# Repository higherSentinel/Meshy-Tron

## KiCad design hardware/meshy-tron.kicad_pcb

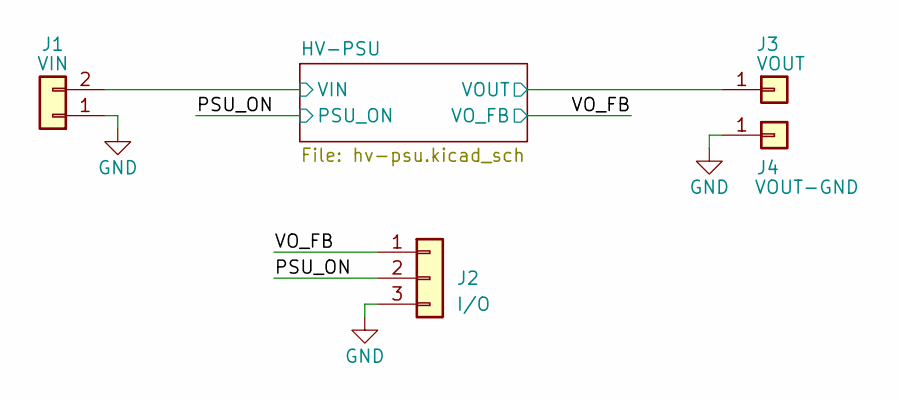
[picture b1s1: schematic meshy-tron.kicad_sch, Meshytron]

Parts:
J1: VIN; PinHeader_1x02_P2.54mm_Vertical
J2: I/O; PinHeader_1x03_P2.54mm_Vertical
J3: VOUT; PinHeader_1x01_P2.54mm_Vertical
J4: VOUT-GND; PinHeader_1x01_P2.54mm_Vertical

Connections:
/HV-PSU/VIN: J1.2; also elsewhere on the board
/HV-PSU/VOUT: J3.1; also elsewhere on the board
/PSU_ON: J2.2; also elsewhere on the board
/VO_FB: J2.1; also elsewhere on the board
GND: J1.1, J2.3, J4.1; also elsewhere on the board

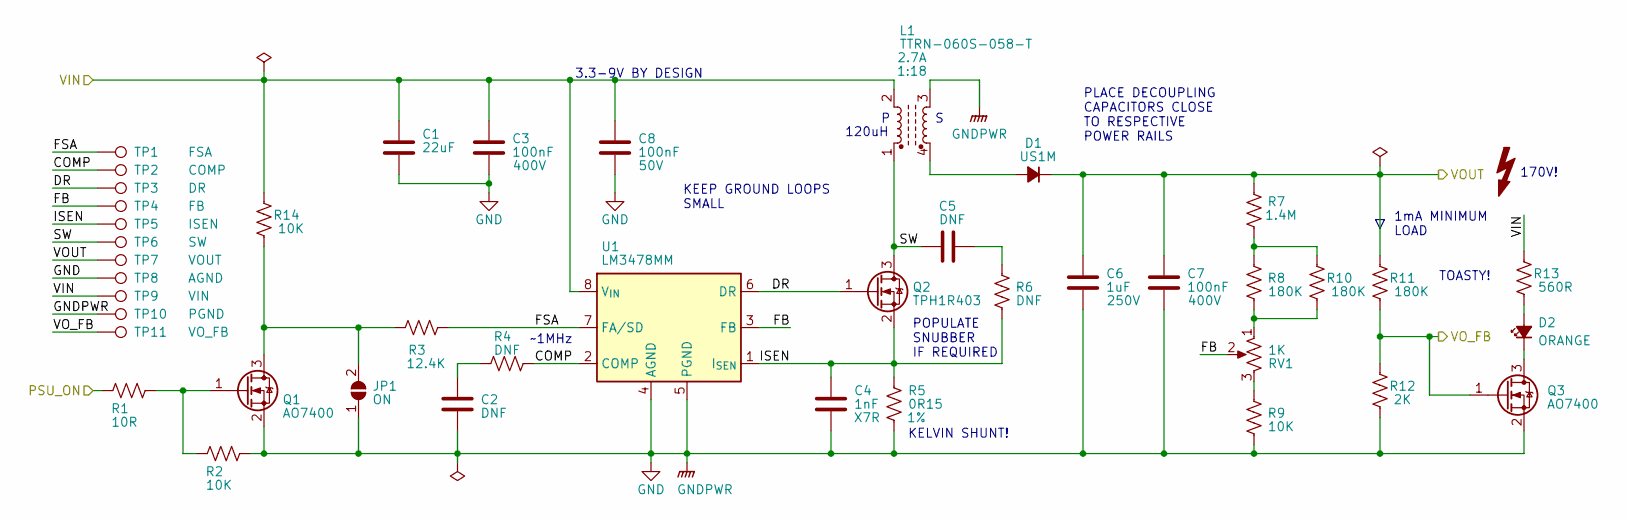
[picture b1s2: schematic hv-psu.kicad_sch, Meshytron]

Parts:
C1: 22uF; C_0603_1608Metric_Pad1.08x0.95mm_HandSolder; MPN CL31A226KAHNNNE; LCSC C12891
C2, C5: DNF; C_0603_1608Metric_Pad1.08x0.95mm_HandSolder
C3, C7: 100nF; C_1206_3216Metric_Pad1.33x1.80mm_HandSolder; Voltage 400V; MPN FM31X104K251EEG; LCSC C365814
C4: 1nF; C_0603_1608Metric_Pad1.08x0.95mm_HandSolder; MPN CL10B102KB8NNNC; LCSC C1588
C6: 1uF; C_1812_4532Metric_Pad1.57x3.40mm_HandSolder; Voltage 250V; Tolerance X7R; MPN FS43X105K251EGG; LCSC C381468
C8: 100nF; C_0603_1608Metric_Pad1.08x0.95mm_HandSolder; Voltage 50V; MPN 0603B104K500NT; LCSC C30926
D1: US1M; D_SMA_Handsoldering; MPN US1M; LCSC C412437
D2: ORANGE; LED_0805_2012Metric_Pad1.15x1.40mm_HandSolder; MPN SZYY0805O; LCSC C434437
JP1: ON; SolderJumper-2_P1.3mm_Open_RoundedPad1.0x1.5mm
L1: TTRN-060S-058-T; MPN TTRN-060S-058-T
Q1, Q3: AO7400; SOT-323_SC-70_Handsoldering; MPN AO7400-VB; LCSC C879165
Q2: TPH1R403; SOP-ADVANCED; MPN TPH1R403NL; LCSC C83440
R1: 10R; R_0603_1608Metric_Pad0.98x0.95mm_HandSolder; MPN 0603WAF100JT5E; LCSC C22859
R2, R9, R14: 10K; R_0603_1608Metric_Pad0.98x0.95mm_HandSolder; MPN RC0603JR-0710KL; LCSC C99198
R3: 12.4K; R_0603_1608Metric_Pad0.98x0.95mm_HandSolder; MPN RS-03K1242FT; LCSC C310267
R4, R6: DNF; R_0603_1608Metric_Pad0.98x0.95mm_HandSolder
R5: 0R15; R_1206_3216Metric_Pad1.30x1.75mm_HandSolder; Tolerance 1%; MPN RL1206FR-070R15L; LCSC C327070
R7: 1.4M; R_0603_1608Metric_Pad0.98x0.95mm_HandSolder; MPN CR1206F41404G; LCSC C3037104
R8, R10, R11: 180K; R_1210_3225Metric_Pad1.30x2.65mm_HandSolder; MPN FRC1210J184-TS; LCSC C2960705
R12: 2K; R_0603_1608Metric_Pad0.98x0.95mm_HandSolder; MPN 0603WAF2001T5E; LCSC C22975
R13: 560R; R_0603_1608Metric_Pad0.98x0.95mm_HandSolder; MPN 0805W8F5600T5E; LCSC C28636
RV1: 1K; Potentiometer_Bourns_3224W_Vertical; MPN BOURNS 3224W-1-102E; LCSC C50204
TP1: FSA; TestPoint_Pad_D1.0mm
TP2: COMP; TestPoint_Pad_D1.0mm
TP3: DR; TestPoint_Pad_D1.0mm
TP4: FB; TestPoint_Pad_D1.0mm
TP5: ISEN; TestPoint_Pad_D1.0mm
TP6: SW; TestPoint_Pad_D1.0mm
TP7: VOUT; TestPoint_Pad_D1.0mm
TP8: AGND; TestPoint_Pad_D1.0mm
TP9: VIN; TestPoint_Pad_D1.0mm
TP10: PGND; TestPoint_Pad_D1.0mm
TP11: VO_FB; TestPoint_Pad_D1.0mm
U1: LM3478MM; VSSOP-8_3.0x3.0mm_P0.65mm; MPN LM3478MMX/NOPB; LCSC C404045

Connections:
/HV-PSU/COMP: R4.2, TP2.1, U1.2 (COMP)
/HV-PSU/DR: Q2.1 (G), TP3.1, U1.6 (DR)
/HV-PSU/FB: RV1.2, TP4.1, U1.3 (FB)
/HV-PSU/FSA: R3.2, TP1.1, U1.7 (FA/SD)
/HV-PSU/ISEN: C4.1, Q2.2 (S), R5.2, R6.1, TP5.1, U1.1 (I_{SEN})
/HV-PSU/SW: C5.1, L1.1, Q2.3 (D), TP6.1
/HV-PSU/VIN: C1.1, C3.1, C8.1, L1.2, R13.2, R14.2, TP9.1, U1.8 (V_{IN}); also elsewhere on the board
/HV-PSU/VOUT: C6.1, C7.1, D1.1 (K), R7.1, R11.2, TP7.1; also elsewhere on the board
/PSU_ON: R1.2; also elsewhere on the board
/VO_FB: Q3.1 (G), R11.1, R12.2, TP11.1; also elsewhere on the board
GND: C1.2, C2.2, C3.2, C4.2, C6.2, C7.2, C8.2, JP1.1 (A), L1.3, Q1.2 (S), Q3.2 (S), R2.1, R5.1, R9.1, R12.1, TP8.1, TP10.1, U1.4 (AGND), U1.5 (PGND); also elsewhere on the board
unnamed: C2.1, R4.1
unnamed: C5.2, R6.2
unnamed: D1.2 (A), L1.4
unnamed: D2.1 (K), Q3.3 (D)
unnamed: D2.2 (A), R13.1
unnamed: JP1.2 (B), Q1.3 (D), R3.1, R14.1
unnamed: Q1.1 (G), R1.1, R2.2
unnamed: R9.2, RV1.3
unnamed: R8.1, R10.1, RV1.1
unnamed: R7.2, R8.2, R10.2

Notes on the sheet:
TOASTY!
PLACE DECOUPLING CAPACITORS CLOSE TO RESPECTIVE POWER RAILS
KELVIN SHUNT!
~1MHz
170V!
120uH
3.3-9V BY DESIGN
POPULATE SNUBBER IF REQUIRED
1mA MINIMUM LOAD
KEEP GROUND LOOPS SMALL

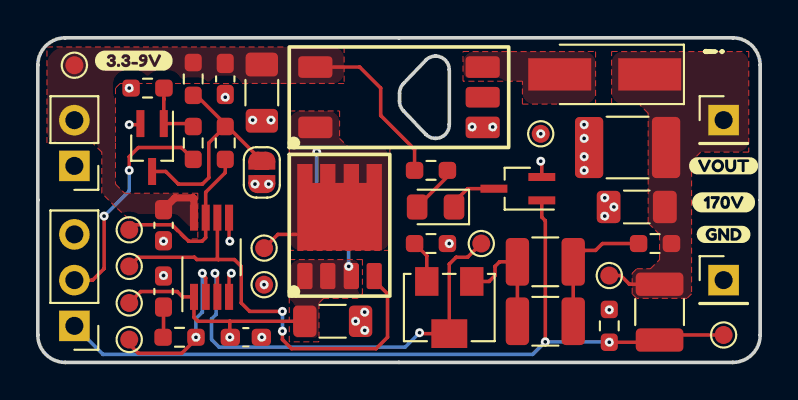
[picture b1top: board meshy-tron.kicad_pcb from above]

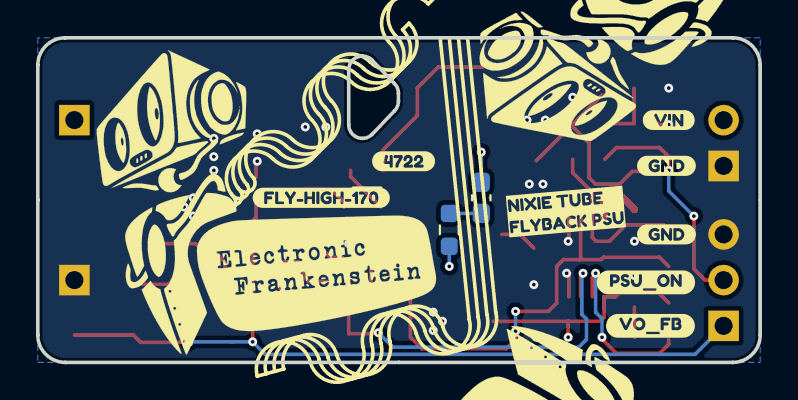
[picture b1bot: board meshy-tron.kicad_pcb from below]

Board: 2 copper layers, 40.1 x 18.0 mm, 58 parts (10 on the bottom side), 21 nets.

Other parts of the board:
kibuzzard-63828ECC: G***; kibuzzard-63828ECC
kibuzzard-63828EDB: G***; kibuzzard-63828EDB
kibuzzard-63829B28: G***; kibuzzard-63829B28
kibuzzard-63829C5B: G***; kibuzzard-63829C5B
kibuzzard-63829F7F: G***; kibuzzard-63829F7F
kibuzzard-63829F8D: G***; kibuzzard-63829F8D
kibuzzard-63829F70: G***; kibuzzard-63829F70
kibuzzard-63829FA8: G***; kibuzzard-63829FA8
kibuzzard-63829FB9: G***; kibuzzard-63829FB9
kibuzzard-638295AD: G***; kibuzzard-638295AD
kibuzzard-638295D5: G***; kibuzzard-638295D5
kibuzzard-63829606: G***; kibuzzard-63829606

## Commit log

2022-12-14 feat(hv-psu): completed design and PCB layout - hvpsu based on the LM3478 - 3.3-9V operation [to be tested]
